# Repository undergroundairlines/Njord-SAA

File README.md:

# Njord-SAA
The Njord SAA (Submersible Amphibius Aircraft) is a submersible aircraft which can transition automatically from underwater travel to aerial flight. To resurface, it can empty it's 2 ballast tanks, pitch almost 90° directly up, and launch itself above the surface. When the surface is breached, it deploys 2 sets (yes, that means 4 wings total) of wings, and switches motors to a much higher RPM to produce enough thrust for flight.
The reason for this project was we thought a amphibius aircraft so we designed It. We always wanted a drone/plane and this was our best chance to get one.

# Features 
* Deployable wings: The main visual feature of the Njord SAA is its wings, having 2 sets of deployable wings which allow having good hydrodynamics underwater, while still being able to produce enough lift to fly. The rear set of wings deploy forwards and meet the forward most wings at their tips.

* ~1.5:1 Thrust to Weight Ratio: Due to having 2 large 3 bladed props, and motors that are way too overpowered, at max thrust it will be able to produce mor than the crafts weight in thrust. This will make it incredibly fast, decently manouverable, and much cooler!

* Tailerons: Due to the wings being deployable, there is not enough room to house servos for the ailerons. No matter! Instead, we will repurpose the elevators (and possibly rudders as well) to do both pitch and roll.

* Auto Land: There will be a sort of Auto land feature to be added eventually, where at the flick of a button the craft can automatically bring itslef to the ground safely, and softly.

* Groud Avoidance System (GAS): Any time the pilot brings the aircraft too close to the ground, it will automatically pull up just before the perfect moment to ensure the pilot remains under control right until it's almost too late. Uses data from the gyro, and laser rangefinder to (semi-realistically) estimate its height, which allows the  computer to know when to pull up.

* As an opposite to the Ground Avoidance System, there will be a system to resurface the craft when submerged if the batteries become dangerously low, or it loses signal.

# CAD
The cad files for the Njord SAA were made in autodesk inventor professional. There are 5 seperate modules for the elevators, wings, tail, body and nose. There were lots of struggles with the cad on multiple occasions, such as how I had to fully redesign the body nose and tail a few times. The main reason for this was because I had very little design constraints to work from, and mostly figured it out as I went.

Nose cone:

Tail:

# PCB
This is the PCB for the Njord SAA! It is a standard 4 layer PCB featuring all elements needed for a flight computer like an IMU, barometer, an ESP32, and many pin headers for devices like servos, motors, and other sensors. It was designed originally in Eagle, but I switched to KiCad bacause there were a lot more sources for help, and it both looks and feels more modern.

Render top:

Wiring diagram:

Schematic:

  # How to buld

  ### !! MAKE SURE TO WEAR PROPER PPE WHEN WORKING ON CURED CARBON FIBER & FIBERGLASS !!
  (resperator and eye protection, full body suit for fiberglass)

 ### Prepare fuselage:
1. 3d print the main body, tail section, tail tip, nose cone, bulkhead, and hatches, then remove supports and clean up the prints
2. Lightly sand the nose cone and main body to ensure a proper adhesion to the epoxy
3. Cut carbon fiber weave to the correct size to wrap the main body, then cut out sections for the wing pins, ESC slots and battery hatches. Do the same for fiberglass to the nose cone
4. Make sure the cuts fit the subsequent part BEFORE mixing any epoxy
5. Mix 2 part epoxy in the correct ratio supplied by the manufacturer, then with a foam roller wet out cuts on both sides and squeeze out the excess epoxy
6. Wrap the carbon fiber around the body section, smooth out any wrinkles and air pockets, then apply peel ply to the surface. Repeate process for the fiberglass on the nose cone (peel ply is optional for fiberglass) and leave both to cure for 24-48 hours
7. After drying, drill out screw holes (you can shine a light through the holes in the 3d print to see the outline) and dremel the edges of the pre cut sections for wing pins and hatches until their sizes match the 3d print
 ### Prepare Control Surfaces & Wings:
1. 3d print rudders, elevons, and wings, then remove supports and clean up the prints
2. Lightly sand all surfaces of all parts for good adhesion, and pre cut carbon fiber weave to the correct sizes for each part seperately, with cutout areas for the wing bearings
3. Repeat steps 4-7 from the Fuselage Preperation instructions for each part
5. Cut 8mm carbon fiber rods so they will just stick out of the wing spar holes, there are 2 8mm rods in each of the four wings. Coat each rod with Sikaflex, then push as far into the hole as possible and let cure for 12-24 hours. After cured, cut the CF rods as close to the wing as possible and sand or file the rest until it is flush with the wing
6. Press fit a bearing into each wing in the provided slot
7. Repeat step 5, but with 5mm carbon fiber rod and for the back holes only in the elevators
### Install Electronic Hardware:
1. Neatly solder the PCB using the stencil provided by JLCPCB, and plug in the ESP32-S3 DEVKITC along with the MINI-560 buck converter. Make sure that the buck converter and esp32 are placed the correct way around, and test for improperly soldered components
2. Install the following hardware into their respective places:
   * Rear servos; Each servo is held in by 2 screws (make sure the cables get routed through the cable hole), then sealed using Sikaflex for waterproofing.
   * Motors; Install to motor mounts with 4 screws 
   * ESCs; Sikaflex each ESC into the slots, making sure they are facing the correct direction and wires are through the holes. Use more Sikaflex to create a flush surface over the ESCs for aerodynamics
   * Centre servo; Screw 2 screws into internal mount located on the rear of the body section. Connect to all 4 wings' release pins with push rods
   * Ballast Pumps; Slot pump into the slot and Sikaflex it into place. Heat insert the brass tube fittings into the wall holes and ballast tank holes, then connect tubing from pump input to the outside connecter, and the output to the connector on the ballast tank. Repeat for both pumps
   * Batteries: Slide in the two 5200mah batteries into the secure slot in the top and bottom hatches, ensuring the cables go towards the front
   * FS CVT01; Secure one side to the bottom of the forward part of the main body section using either hot glue, or Sikaflex
   * LiDaR; Insert LiDaR into the nose cone and Sikaflex it to solidify its position
   * PCB; Slot PCB into the tray inside the nose cone and screw the 2 screws into the corners
   * iA6B; Insert iA6B below the PCB, with the antenna facing forwards and pins pointing rearwards. Secure in place with hot glue, or Sikaflex
### Cable Routing:
##### Tip: lable each cable before installing so you know what  is what
1. Start with the tail section:
   * Rear servos; Route the servo's cable through the channel for them to bring them to the forwards most part of the tail, and connect a cable extender to the cable. Repeat for all 4 servos
   * Motors; Route the motor cables along the inset channels on the rear side of the motor mount and into the tail. Once into place, use Sikaflex to fill the rest of       the channel and the hole that enters the tail section. Solder and heatshrink a similar thickness cable to each of the 3 wires on the motor, and repeat for both motors
2. Main Body section:
   * ESCs; Route the wires through the holes that lead into the body, and seal the cable holes with Sikaflex. Connect the 3 pin cable to an extender and run it below the wing box to the front of the body, and repeat on the other side. Solder both ESCs' + and - input cables to a single xt-60 connector, making sure to put the + and - the correct way around. Attach an XT-60 cable extender (make it yourself with 2 spare wires and XT-60 connectors) to the plug, and run it down the body with the 3 pin cable
   * Centre Servo; Plug a servo cable extender into the connector, then run it internally below the wing box and out of the front of the body
   * Ballast Pumps; Strip the tip off of 2 spare wires, then twist them to the + and - of the pump. Solder a small amount of solder onto the connection to ensure good connection, then pull a piece of shrink wrap over the exposed wire and shrink with a heat gun. Repeat on both pumps
   * FS CVT01; Cut the connectors off of the two 1 pin cables, and solder them directly to the XT60 connector (make sure the polarity is correct)
3. Nose Cone:
   * LiDaR; Connect 5 pin cable to the "GY-TOF10M" labled 5 pin header on the pcb
   * iA6B; Plug a 3 pin cable into the "Servo" section on the iA6B, and connect it to the horizontal 3 pin header on the pcb. Optionally, you can shorten the  3 pin cable by cutting it to length, removing the connector, and re soldering it to the fixed length
### Final Assembly:
##### Connect tail section and main body:
 1. Solder and heatshrink the 3 motor cables to the matching 3 cables on the ESC. Repeat on both motors
 2. Route servo cables down the body section along with the cables already going that direction
 3. Slide the body section half way into the tail's slot, then lightly coat the inner wall of the outer rim of the tail section with Sikaflex and slide it fully in. Moving quickly, Screw in the tail section to the body through the 4 screw holes, placing a bead of Sikaflex below the screw's head before fully screwing it in
##### Install Bulkhead:
 1. Pass all loose cables hanging out of the body section through the hole in the bulkhead, and plug in the following cables to the PCB:
       * Servos; Servo plugs on the PCB are labled, and connect as follows: servo 1: left elevon, servo 2: right elevon, servo 3: top rudder, servo 4: bottom rudder, and servo 5: wing release servo
       * ESCs; 3 pin cables plug into "ESC_1" for left ESC and "ESC_2" for right ESC
       * Ballast Pumps; connect cables to screw terminals "Pump_1" and "Pump_2". It does not matter which side connects to which terminal
       * FS CVT01; DOES NOT PLUG INTO PCB, instead it plugs into the "sense" plug on the radio reciever
 2. Put bulkhead far enough from the nose to fit a screw driver to the 2 PCB screws, and pull all cables through the bulkhead to this length. Sikaflex the cable hole completely shut to prevent any leaking
 3. Insert O-ring into the groove in the nose cone and push the bulkhead into the nose cone. Screw in all 8 screws in a star pattern to fully seal the nose, with a bead of Sikaflex enderneath each screw's head
##### Attach nose cone to body:
 1. Drop a bead of Sikaflex onto the nose cone's outer rim and slide the body into the nose cone's slot.
 2. Screw in the 4 screws around the attachment area, with a bead of Sikaflex below each screw's head
##### Attach wings:
 1. Insert the wing into the wing slot, ensuring that the leading edge of the wing is facing outwards of the body
 2. Push an 8mm CF rod into the hole in the body that corresponds to the wing, and cut it down to a size where you can file the rest
##### Attach elevators and rudders:
 1. Place a 5mm CF rod loosely into the front hole of the left elevator
 2. Push the other side of the CF rod through the hole located just in front of the elevator servo, and place the right elevator on the other end of the CF rod
 3. Attach pushrods to both servos that attach to each elevator
 4. Slot rudders into the hinge joints located on the top and bottom of the tail, and insert a 2mm steel rod (you can cut up a push rod to use as this) into the hinge and   attach onto the hings with a small bead of Sikaflex
 5. Attach rudders to rudder servos with a push rod
##### Final attachments:
 1. Connect the props to the motors with the nut that screws into the motor shaft. Make sure the props are facing the correct way
 2. Attach the hatches by putting a small amount of Sikaflex around the channels on the body, then press them in
### Firmware:
 1. Download firmware from Github page
 2. Connect ESP32 to computer via the USB-C port on the ESP32
 3. Upload the firmware onto the board

### Conquer the seas and skies!

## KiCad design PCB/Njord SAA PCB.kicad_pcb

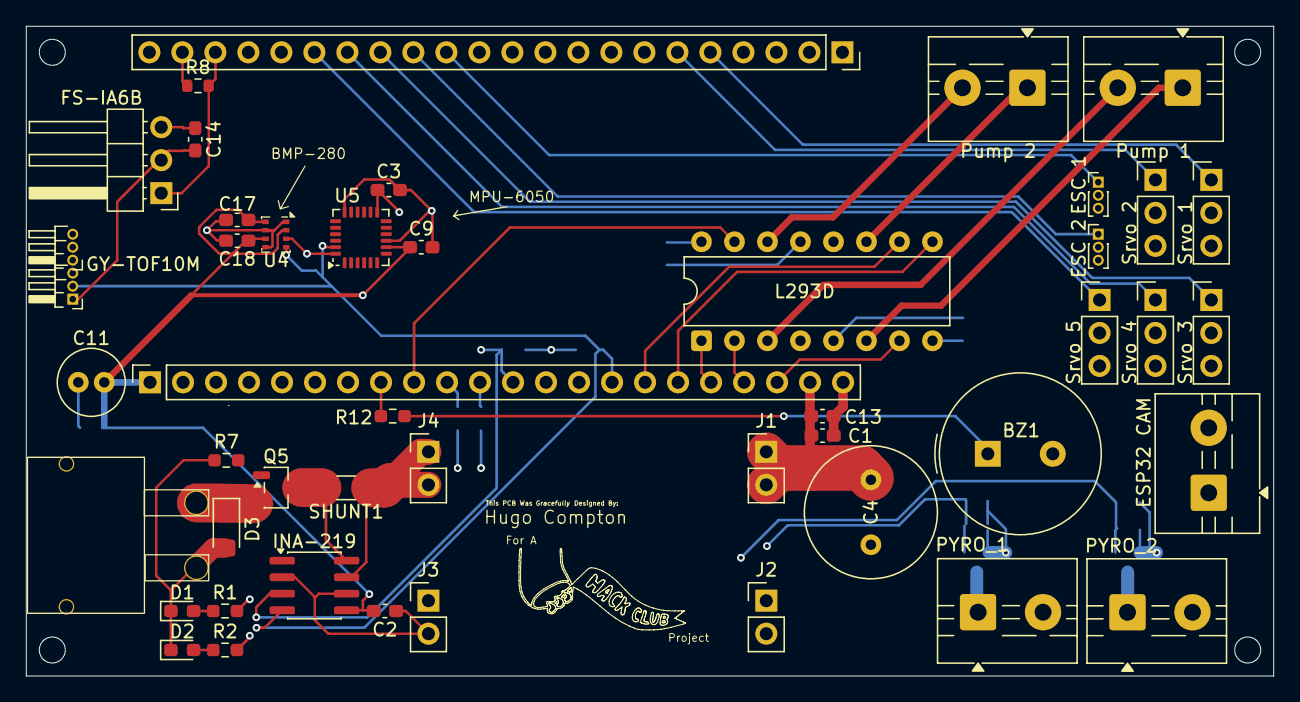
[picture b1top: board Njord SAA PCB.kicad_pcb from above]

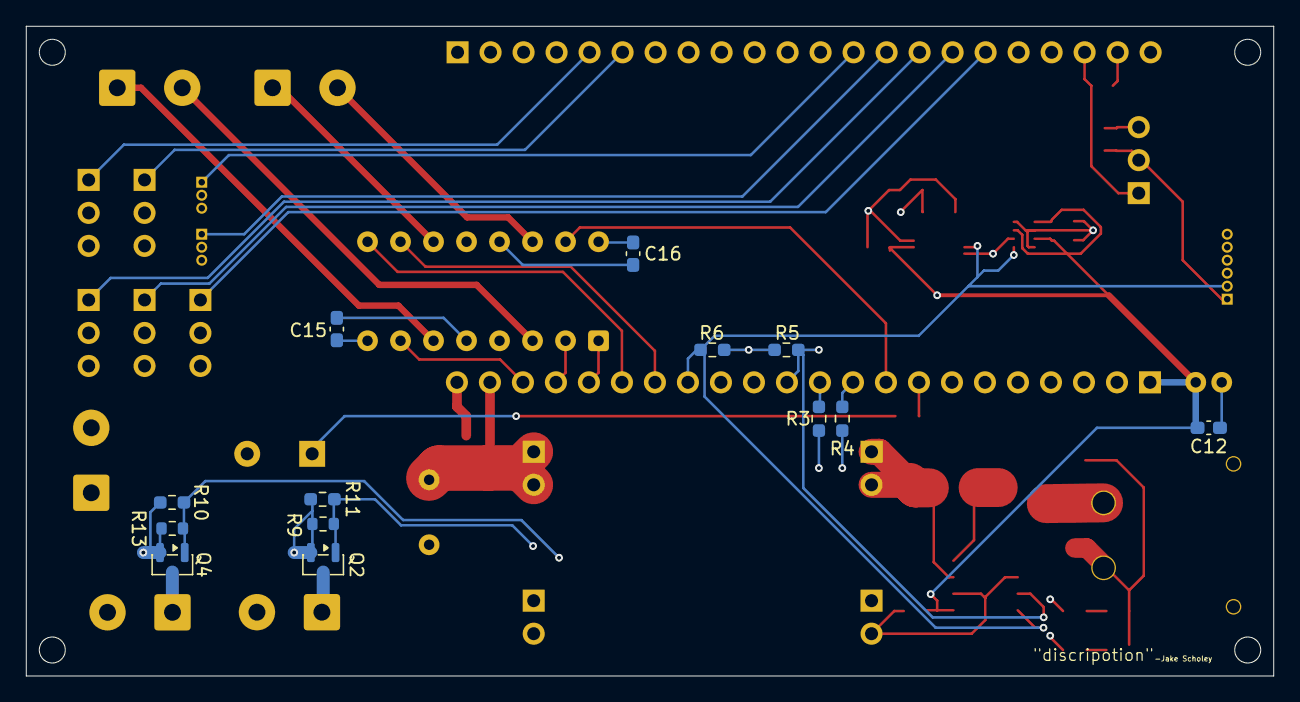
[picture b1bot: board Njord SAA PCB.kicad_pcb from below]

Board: 4 copper layers, 96.0 x 50.0 mm, 60 parts (13 on the bottom side), 40 nets.

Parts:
BZ1: Buzzer; Buzzer_TDK_PS1240P02BT_D12.2mm_H6.5mm
C1: 1uF; C_0603_1608Metric_Pad1.08x0.95mm_HandSolder
C2, C3, C9, C12, C13, C14, C16, C17, C18: 0.1uF; C_0603_1608Metric_Pad1.08x0.95mm_HandSolder
C4: 1000uF; C_Radial_D10.0mm_H20.0mm_P5.00mm
C11: 68uF; C_Radial_D5.0mm_H11.0mm_P2.00mm
C15: 10uF; C_0603_1608Metric_Pad1.08x0.95mm_HandSolder
D1: GRN LED; LED_0603_1608Metric_Pad1.05x0.95mm_HandSolder
D2: RED LED; LED_0603_1608Metric_Pad1.05x0.95mm_HandSolder
D3: SMF10A; D_SMF
ESC 1, ESC 2: Conn_01x03_Pin; PinHeader_1x03_P1.00mm_Vertical
ESP32, ESP32_L1: Conn_01x22_Socket; PinSocket_1x22_P2.54mm_Vertical
ESP32 CAM: Screw_Terminal_01x02; TerminalBlock_MaiXu_MX126-5.0-02P_1x02_P5.00mm
FS-IA6B: Conn_01x03_Pin; PinHeader_1x03_P2.54mm_Horizontal
GY-TOF10M: Conn_01x03_Pin; PinHeader_1x03_P1.00mm_Horizontal
INA-219: INA219AxD; SOIC-8_3.9x4.9mm_P1.27mm
J1: V+OUT; PinHeader_1x02_P2.54mm_Vertical
J2: V-OUT; PinHeader_1x02_P2.54mm_Vertical
J3: V-IN; PinHeader_1x02_P2.54mm_Vertical
J4: V+IN; PinHeader_1x02_P2.54mm_Vertical
J7: Conn_01x03_Pin; PinHeader_1x03_P1.00mm_Horizontal
L293D: L293; DIP-16_W7.62mm
PYRO_1, PYRO_2: Screw_Terminal_01x02; TerminalBlock_MaiXu_MX126-5.0-02P_1x02_P5.00mm
Pump 1: Ballast Pump 1; TerminalBlock_MaiXu_MX126-5.0-02P_1x02_P5.00mm
Pump 2: Ballast Pump 2; TerminalBlock_MaiXu_MX126-5.0-02P_1x02_P5.00mm
Q2, Q4: Si2302; SOT-23
Q5: Q_PMOS_GSD; SOT-23-3
R1, R3, R4, R12: 100R; R_0603_1608Metric_Pad0.98x0.95mm_HandSolder
R2: 220R; R_0603_1608Metric_Pad0.98x0.95mm_HandSolder
R5, R6: 4.7kR; R_0603_1608Metric_Pad0.98x0.95mm_HandSolder
R7: 100kR; R_0603_1608Metric_Pad0.98x0.95mm_HandSolder
R8: 1kR; R_0603_1608Metric
R9, R13: 10kR; R_0603_1608Metric
R10, R11: 10kR; R_0603_1608Metric_Pad0.98x0.95mm_HandSolder
SHUNT1: 10mR; R_1206_3216Metric_Pad1.30x1.75mm_HandSolder
Srvo 1, Srvo 2, Srvo 3, Srvo 4, Srvo 5: Motor_Servo; PinHeader_1x03_P2.54mm_Vertical
U3: 2s LiPo Connector; XT-30
U4: BMP280; Bosch_LGA-8_2x2.5mm_P0.65mm_ClockwisePinNumbering
U5: MPU-6050; InvenSense_QFN-24_4x4mm_P0.5mm

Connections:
+3.3V: C2.2, C3.1, C9.1, C11.2, C12.2, C17.1, C18.1, ESP32_L1.1, INA-219.5 (VS), R5.1, R6.2, U4.2 (CSB), U4.6 (VDDIO), U4.8 (VDD), U5.8 (VLOGIC), U5.13 (VDD)
+5V: C1.1, C4.1, C13.1, C14.2, C15.1, C16.2, ESP32 CAM.1, ESP32_L1.21, FS-IA6B.2, GY-TOF10M.1, J1.1, J1.2, L293D.8 (VCC2), L293D.16 (VCC1), PYRO_1.2, PYRO_2.2, Srvo 1.2 (+), Srvo 2.2 (+), Srvo 3.2 (+), Srvo 4.2 (+), Srvo 5.2 (+)
/1A: ESP32_L1.19, L293D.2 (1A)
/2A: ESP32_L1.20, L293D.7 (2A)
/3A: ESP32_L1.16, L293D.10 (3A)
/4A: ESP32_L1.9, L293D.15 (4A)
/BUZZER: ESP32_L1.8, R12.2
/Ballast Pump 1 +: L293D.3 (1Y), Pump 1.2
/Ballast Pump 1 -: L293D.6 (2Y), Pump 1.1
/Ballast Pump 2 +: L293D.11 (3Y), Pump 2.1
/Ballast Pump 2 -: L293D.14 (4Y), Pump 2.2
/EN1,2: ESP32_L1.18, L293D.1 (EN1,2)
/EN3,4: ESP32_L1.17, L293D.9 (EN3,4)
/ESC_1: ESC 1.1, ESP32.13
/ESC_2: ESC 2.1, ESP32.14
/GRN LED: ESP32_L1.4, R1.2
/PYRO 1: ESP32_L1.11, R3.2
/PYRO 2: ESP32_L1.10, R4.2
/RED LED: ESP32_L1.5, R2.2
/RX: ESP32.20, FS-IA6B.1, R8.2
/SCL: ESP32_L1.15, GY-TOF10M.2, INA-219.4 (SCL), R6.1, U4.4 (SCK), U5.23 (SCL)
/SDA: ESP32_L1.12, GY-TOF10M.3, INA-219.3 (SDA), R5.2, U4.3 (SDI), U5.24 (SDA)
/Servo 1: ESP32.5, Srvo 1.1 (PWM)
/Servo 2: ESP32.6, Srvo 2.1 (PWM)
/Servo 3: ESP32.15, Srvo 3.1 (PWM)
/Servo 4: ESP32.16, Srvo 4.1 (PWM)
/Servo 5: ESP32.17, Srvo 5.1 (PWM)
/TX: ESP32.21, R8.1
GND: BZ1.2 (-), C1.2, C2.1, C3.2, C4.2, C9.2, C11.1, C12.1, C13.2, C14.1, C15.2, C16.1, C17.2, C18.2, D1.1 (K), D2.1 (K), D3.2 (A2), ESC 1.3, ESC 2.3, ESP32.1, ESP32.2, ESP32.22, ESP32 CAM.2, ESP32_L1.22, FS-IA6B.3, INA-219.2 (A0), INA-219.6 (GND), J2.1, J2.2, J3.1, J3.2, J7.3 (Pin_3_3), L293D.4 (GND), L293D.5 (GND), L293D.12 (GND), L293D.13 (GND), Q2.2 (S), Q4.2 (S), R7.1, R9.1, R10.2, R11.2, R13.1, Srvo 1.3 (-), Srvo 2.3 (-), Srvo 3.3 (-), Srvo 4.3 (-), Srvo 5.3 (-), U3.4 (V-_OUT), U4.1 (GND), U4.5 (SDO), U4.7 (GND), U5.9 (AD0), U5.18 (GND)
unnamed: BZ1.1 (+), R12.1
unnamed: D1.2 (A), R1.1
unnamed: D2.2 (A), R2.1
unnamed: D3.1 (A1), Q5.2 (S), U3.3 (V+_OUT)
unnamed: INA-219.7 (IN-), J4.1, J4.2, SHUNT1.1
unnamed: PYRO_1.1, Q2.3 (D)
unnamed: PYRO_2.1, Q4.3 (D)
unnamed: Q2.1 (G), R3.1, R9.2, R11.1
unnamed: Q4.1 (G), R4.1, R10.1, R13.2
unnamed: INA-219.8 (IN+), Q5.3 (D), SHUNT1.2
unnamed: Q5.1 (G), R7.2

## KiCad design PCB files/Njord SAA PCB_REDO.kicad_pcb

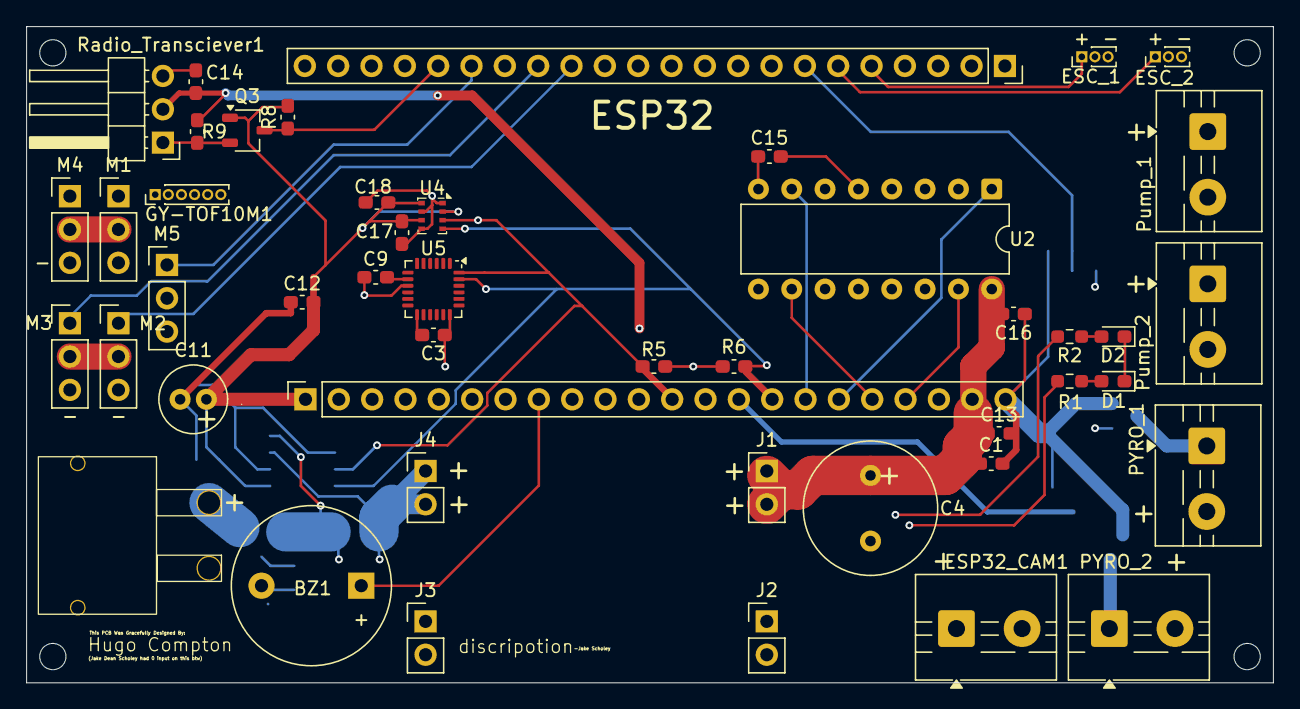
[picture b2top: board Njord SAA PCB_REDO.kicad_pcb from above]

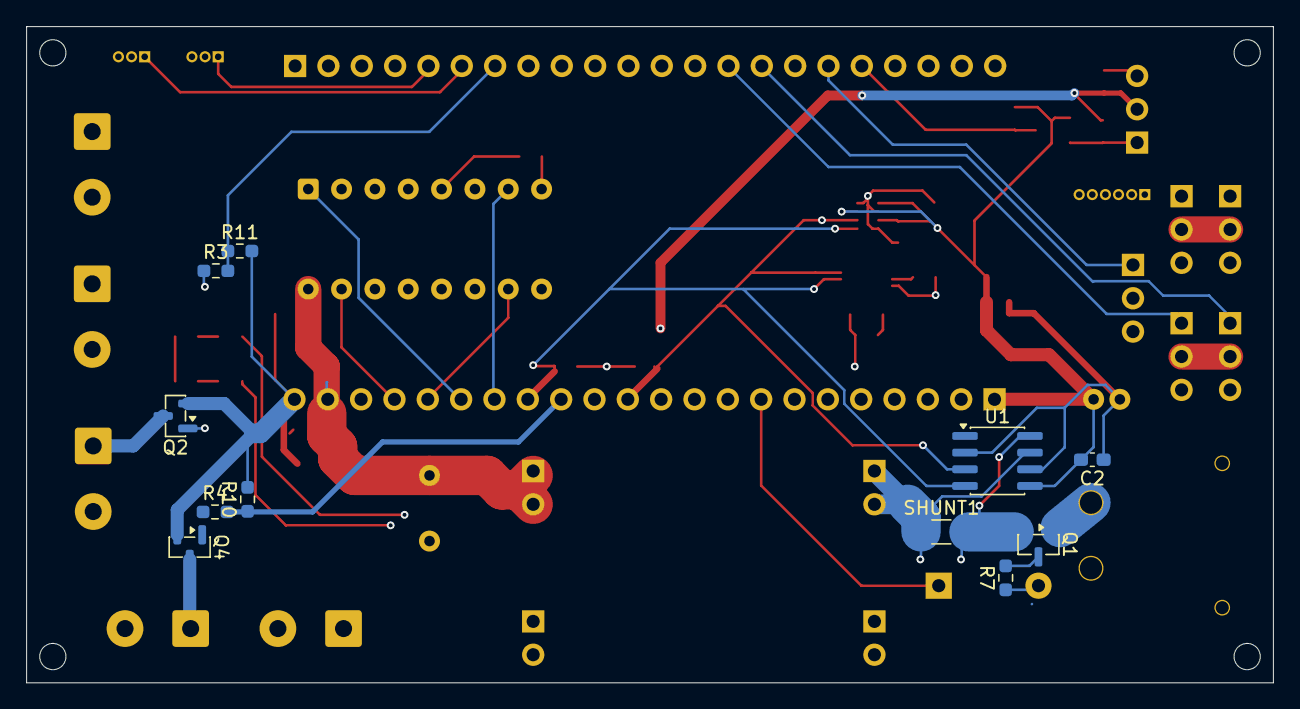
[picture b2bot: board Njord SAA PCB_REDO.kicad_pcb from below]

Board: 4 copper layers, 95.0 x 50.0 mm, 57 parts (11 on the bottom side), 39 nets.

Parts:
BZ1: Buzzer; Buzzer_12x9.5RM7.6
C1: 1uF; C_0603_1608Metric_Pad1.08x0.95mm_HandSolder
C2, C3, C9, C12, C13, C14, C16, C17, C18: 0.1uF; C_0603_1608Metric_Pad1.08x0.95mm_HandSolder
C4: 1000uF; C_Radial_D10.0mm_H20.0mm_P5.00mm
C11: 68uF; C_Radial_D5.0mm_H11.0mm_P2.00mm
C15: 10uF; C_0603_1608Metric_Pad1.08x0.95mm_HandSolder
D1: GRN LED; LED_0603_1608Metric_Pad1.05x0.95mm_HandSolder
D2: RED LED; LED_0603_1608Metric_Pad1.05x0.95mm_HandSolder
ESC_1, ESC_2: Conn_01x03_Pin; PinHeader_1x03_P1.00mm_Vertical
ESP32, ESP32_L1: Conn_01x22_Socket; PinSocket_1x22_P2.54mm_Vertical
ESP32_CAM1: Screw_Terminal_01x02; TerminalBlock_MaiXu_MX126-5.0-02P_1x02_P5.00mm
GY-TOF10M1: Conn_01x06_Pin; PinHeader_1x06_P1.00mm_Vertical
J1: V+OUT; PinHeader_1x02_P2.54mm_Vertical
J2: V-OUT; PinHeader_1x02_P2.54mm_Vertical
J3: V-IN; PinHeader_1x02_P2.54mm_Vertical
J4: V+IN; PinHeader_1x02_P2.54mm_Vertical
M1, M2, M3, M4, M5: Motor_Servo; PinHeader_1x03_P2.54mm_Vertical
PYRO_1, PYRO_2: Screw_Terminal_01x02; TerminalBlock_MaiXu_MX126-5.0-02P_1x02_P5.00mm
Pump_1: Ballast Pump 1; TerminalBlock_MaiXu_MX126-5.0-02P_1x02_P5.00mm
Pump_2: Ballast Pump 2; TerminalBlock_MaiXu_MX126-5.0-02P_1x02_P5.00mm
Q1: Q_PMOS_DSG; SOT-23
Q2, Q4: Si2302; SOT-23
Q3: Q_NMOS_GSD; TSOT-23
R1, R3, R4: 100R; R_0603_1608Metric_Pad0.98x0.95mm_HandSolder
R2: 220R; R_0603_1608Metric_Pad0.98x0.95mm_HandSolder
R5, R6: 4.7kR; C_0603_1608Metric_Pad1.08x0.95mm_HandSolder
R7: 100kR; R_0603_1608Metric_Pad0.98x0.95mm_HandSolder
R8: 3K3; C_0603_1608Metric_Pad1.08x0.95mm_HandSolder
R9: 4K7; C_0603_1608Metric_Pad1.08x0.95mm_HandSolder
R10, R11: 10kR; R_0603_1608Metric_Pad0.98x0.95mm_HandSolder
Radio_Transciever1: Conn_01x03_Pin; PinHeader_1x03_P2.54mm_Horizontal
SHUNT1: 10mR; R_1206_3216Metric_Pad1.30x1.75mm_HandSolder
U1: INA219AxD; SOIC-8_3.9x4.9mm_P1.27mm
U2: L293; DIP-16_W7.62mm
U3: 2s LiPo Connector; XT-30
U4: BMP280; Bosch_LGA-8_2x2.5mm_P0.65mm_ClockwisePinNumbering
U5: MPU-6050; InvenSense_QFN-24_4x4mm_P0.5mm

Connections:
+3.3V: C2.2, C3.1, C9.1, C11.2, C12.2, C17.1, C18.1, ESP32_L1.1, Q3.1 (G), R8.2, U1.5 (VS), U4.2 (CSB), U4.6 (VDDIO), U4.8 (VDD), U5.8 (VLOGIC), U5.13 (VDD)
+5V: C1.1, C4.1, C13.1, C14.2, C15.1, C16.2, ESP32_CAM1.1, ESP32_L1.21, GY-TOF10M1.1, J1.1, J1.2, M1.2 (+), M2.2 (+), M3.2 (+), M4.2 (+), M5.2 (+), PYRO_1.2, PYRO_2.2, R9.1, Radio_Transciever1.2, U2.8 (VCC2), U2.16 (VCC1)
/1A: ESP32_L1.9, U2.2 (1A)
/2A: ESP32_L1.16, U2.7 (2A)
/3A: ESP32_L1.18, U2.10 (3A)
/4A: ESP32_L1.19, U2.15 (4A)
/BUZZER: BZ1.1 (+), ESP32_L1.8
/Ballast Pump 1 +: Pump_1.1, U2.3 (1Y)
/Ballast Pump 1 -: Pump_1.2, U2.6 (2Y)
/Ballast Pump 2 +: Pump_2.1, U2.11 (3Y)
/Ballast Pump 2 -: Pump_2.2, U2.14 (4Y)
/EN1,2: ESP32_L1.17, U2.1 (EN1,2)
/EN3,4: ESP32_L1.20, U2.9 (EN3,4)
/ESC_1: ESC_1.1, ESP32.5
/ESC_2: ESC_2.1, ESP32.6
/GRN LED: ESP32_L1.4, R1.2
/PYRO 1: ESP32.7, R3.2, R11.1
/PYRO 2: ESP32_L1.14, R4.2, R10.1
/RED LED: ESP32_L1.5, R2.2
/Radio Signal: ESP32.18, Q3.3 (D), R8.1
/SCL: ESP32_L1.15, GY-TOF10M1.2, R6.1, U1.4 (SCL), U4.4 (SCK), U5.23 (SCL)
/SDA: ESP32_L1.12, GY-TOF10M1.3, R5.2, U1.3 (SDA), U4.3 (SDI), U5.24 (SDA)
/Servo 1: ESP32.13, M1.1 (PWM)
/Servo 2: ESP32.14, M2.1 (PWM)
/Servo 3: ESP32.15, M3.1 (PWM)
/Servo 4: ESP32.16, M4.1 (PWM)
/Servo 5: ESP32.17, M5.1 (PWM)
GND: BZ1.2 (-), C1.2, C2.1, C3.2, C4.2, C9.2, C11.1, C12.1, C13.2, C14.1, C15.2, C16.1, C17.2, C18.2, D1.1 (K), D2.1 (K), ESC_1.3, ESC_2.3, ESP32.1, ESP32.2, ESP32.22, ESP32_CAM1.2, ESP32_L1.22, GY-TOF10M1.6, J2.1, J2.2, J3.1, J3.2, M1.3 (-), M2.3 (-), M3.3 (-), M4.3 (-), M5.3 (-), Q2.2 (S), Q4.2 (S), R5.1, R6.2, R7.1, R10.2, R11.2, Radio_Transciever1.3, U1.2 (A0), U1.6 (GND), U2.4 (GND), U2.5 (GND), U2.12 (GND), U2.13 (GND), U3.4 (V-_OUT), U4.1 (GND), U4.5 (SDO), U4.7 (GND), U5.9 (AD0), U5.18 (GND)
unnamed: D1.2 (A), R1.1
unnamed: D2.2 (A), R2.1
unnamed: J4.1, J4.2, SHUNT1.1, U1.7 (IN-)
unnamed: PYRO_1.1, Q2.3 (D)
unnamed: PYRO_2.1, Q4.3 (D)
unnamed: Q1.1 (D), U3.3 (V+_OUT)
unnamed: Q1.3 (G), R7.2
unnamed: Q1.2 (S), SHUNT1.2, U1.8 (IN+)
unnamed: Q2.1 (G), R3.1
unnamed: Q3.2 (S), R9.2, Radio_Transciever1.1
unnamed: Q4.1 (G), R4.1

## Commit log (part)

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2026-05-10 Rename BOM (very unfinished).csv to BOM.csv
2026-05-28 Rename elivators.stp to Elevons.stp
2026-05-28 Rename wing ready for torsiom WITH COOKIE .stp to Front_Wings.stp
2026-05-28 Rename Front_Wings.stp to Front_Wings.stp
2026-05-28 Rename BULK HEAD with half holes.stp to Nose Bulkhead.stp
2026-05-28 Rename big door slotty with toly rinces .5.stp to Bottom Hatch.stp
2026-05-28 Rename top hatchy mo bob.stp to Hatch_Top.stp
2026-05-28 Rename Nose Bulkhead.stp to Nose_Bulkhead.stp
2026-05-28 Rename Bottom Hatch.stp to Hatch_Bottom.stp
2026-05-28 Rename I think done body unless hugo hass a hissy fit part 1 .stp to Body.stp
2026-05-29 Rename refinded nose cone with holes.stp to Nose.stp
2026-05-29 Rename FULL VIRTICAL NO HORISONTAL.stp to Tail.stp
2026-05-29 Rename Gerbers.zip to Gerber.zip
2026-06-02 Rename ziney mobob v 10.pdf to Zine page.pdf
2026-06-02 Rename CAD FILES/I think done body unless hugo hass a hissy fit.ipt to CAD FILES/IPTs/Body Section.ipt
2026-06-02 Rename CAD FILES/elivators s.ipt to CAD FILES/IPTs/Elevons.ipt
2026-06-02 Rename CAD FILES/FULL VIRTICAL NO HORISONTAL.ipt to CAD FILES/IPTs/Tail .ipt
2026-06-02 Rename CAD FILES/back wings smooth .ipt to CAD FILES/IPTs/Wings_Rear.ipt
2026-06-02 Rename CAD FILES/big door slotty with toly rinces .5.ipt to CAD FILES/IPTs/Hatch_Bottom.ipt
2026-06-02 Rename CAD FILES/tail needs servo plug.ipt to CAD FILES/IPTs/Tail Tip.ipt
2026-06-02 Rename CAD FILES/top hatchy mo bob.ipt to CAD FILES/IPTs/Hatch_Top.ipt
2026-06-02 Rename CAD FILES/wing ready for torsiom WITH COOKIE .ipt to CAD FILES/IPTs/Wing_Front
2026-06-02 Rename Tail .ipt to Tail.ipt
2026-06-02 Rename Wing_Front to Wings_Front
2026-06-02 Re-arranged & Renamed the files and folder
